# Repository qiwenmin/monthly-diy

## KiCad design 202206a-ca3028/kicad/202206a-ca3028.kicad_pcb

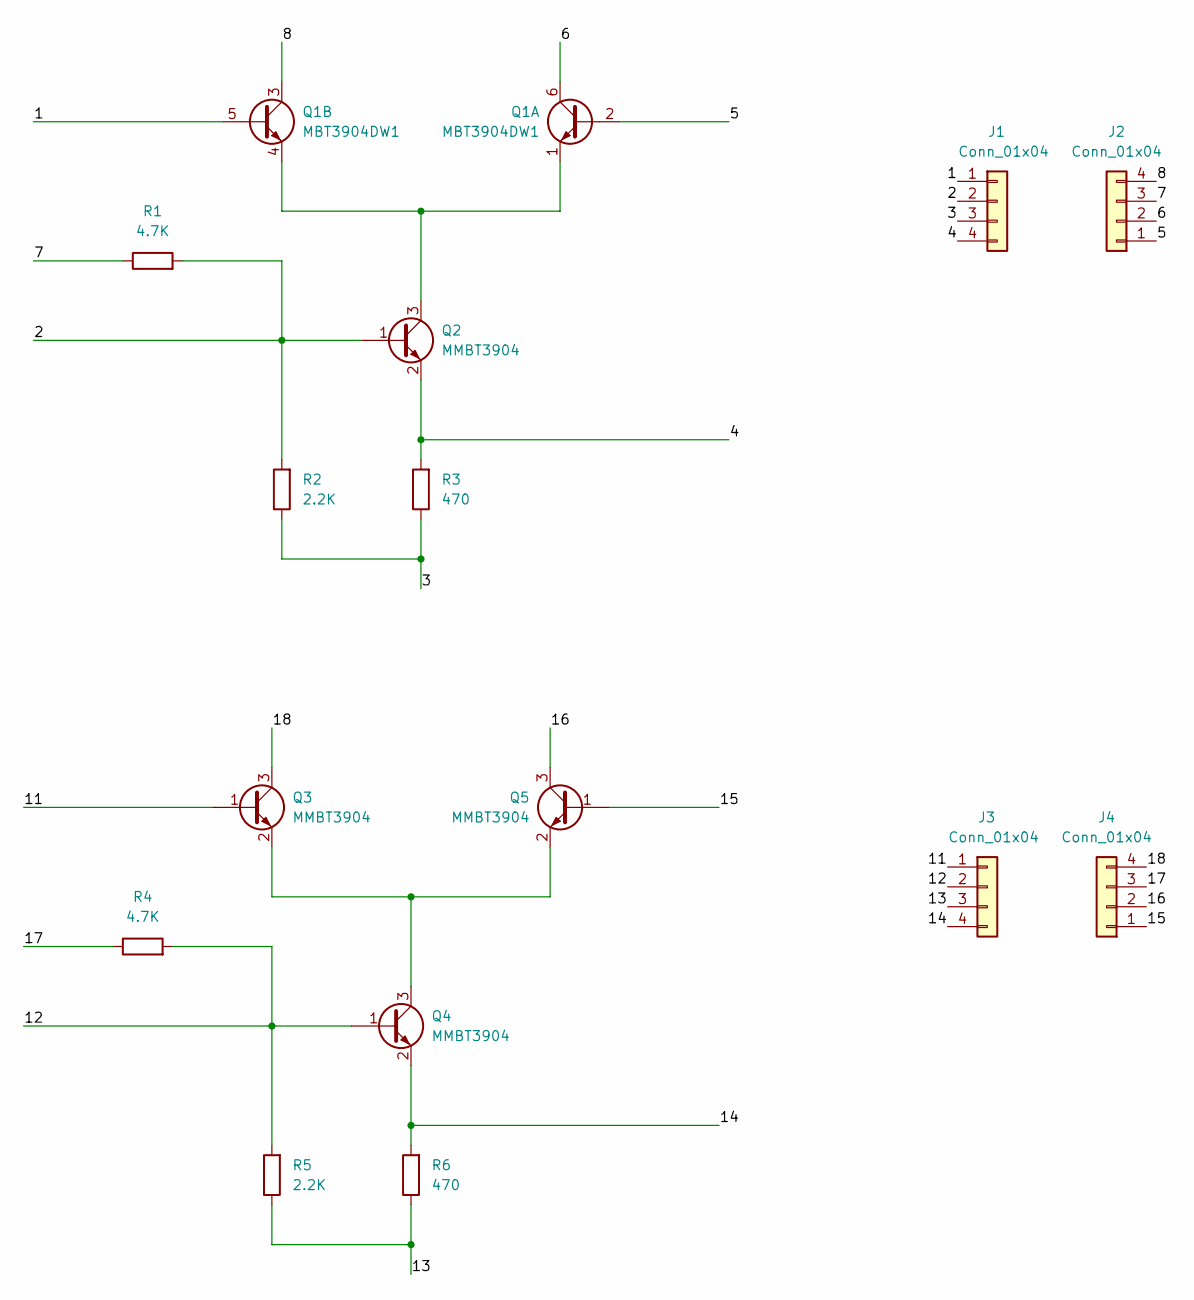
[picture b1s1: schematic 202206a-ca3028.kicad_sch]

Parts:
J1, J2, J3, J4: Conn_01x04; PinHeader_1x04_P2.54mm_Vertical
Q1: MBT3904DW1; SOT-363_SC-70-6
Q2, Q3, Q4, Q5: MMBT3904; SOT-23
R1, R4: 4.7K; R_0805_2012Metric
R2, R5: 2.2K; R_0805_2012Metric
R3, R6: 470; R_0805_2012Metric

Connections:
/1: J1.1, Q1.5 (B2)
/2: J1.2, Q2.1 (B), R1.2, R2.2
/3: J1.3, R2.1, R3.1
/4: J1.4, Q2.2 (E), R3.2
/5: J2.1, Q1.2 (B1)
/6: J2.2, Q1.6 (C1)
/7: J2.3, R1.1
/8: J2.4, Q1.3 (C2)
/11: J3.1, Q3.1 (B)
/12: J3.2, Q4.1 (B), R4.2, R5.2
/13: J3.3, R5.1, R6.1
/14: J3.4, Q4.2 (E), R6.2
/15: J4.1, Q5.1 (B)
/16: J4.2, Q5.3 (C)
/17: J4.3, R4.1
/18: J4.4, Q3.3 (C)
unnamed: Q1.1 (E1), Q1.4 (E2), Q2.3 (C)
unnamed: Q3.2 (E), Q4.3 (C), Q5.2 (E)

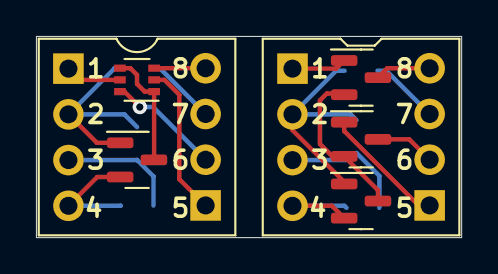
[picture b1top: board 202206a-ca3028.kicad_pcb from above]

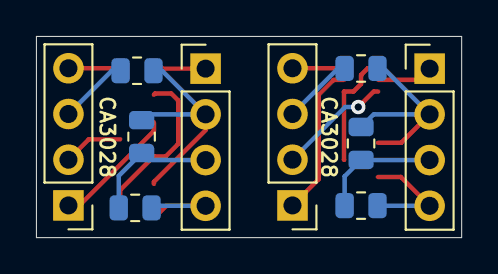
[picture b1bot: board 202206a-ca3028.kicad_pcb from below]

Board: 2 copper layers, 23.6 x 11.2 mm, 15 parts (10 on the bottom side), 18 nets.

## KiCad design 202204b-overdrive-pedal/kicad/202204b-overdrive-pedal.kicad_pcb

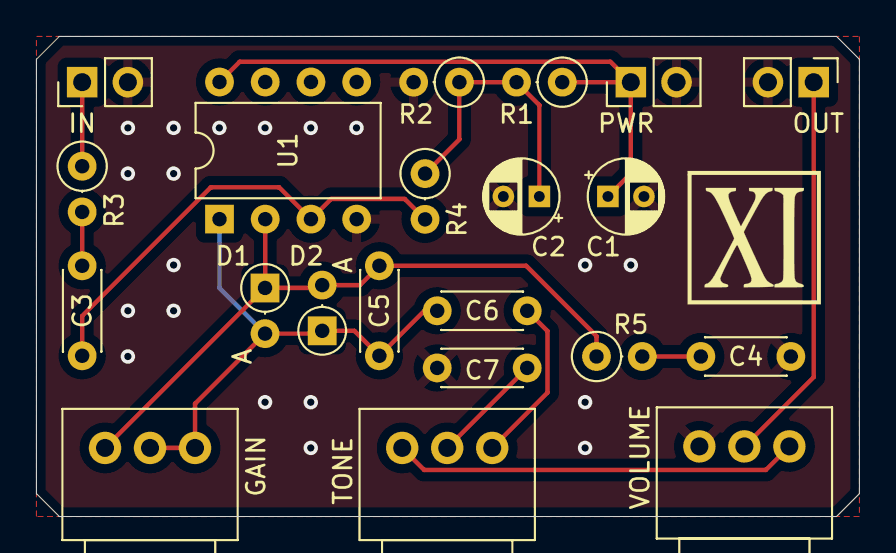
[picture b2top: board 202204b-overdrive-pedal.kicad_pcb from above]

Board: 2 copper layers, 45.7 x 26.7 mm, 21 parts (0 on the bottom side), 13 nets.

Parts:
C1, C2: 47u; CP_Radial_D4.0mm_P2.00mm
C3: 470n; C_Disc_D4.3mm_W1.9mm_P5.00mm
C4: 220n; C_Disc_D4.3mm_W1.9mm_P5.00mm
C5: 100p; C_Disc_D4.3mm_W1.9mm_P5.00mm
C6: 1u; C_Disc_D4.3mm_W1.9mm_P5.00mm
C7: 22n; C_Disc_D4.3mm_W1.9mm_P5.00mm
D1, D2: 1N4148; D_DO-35_SOD27_P2.54mm_Vertical_AnodeUp
J1: PWR; PinHeader_1x02_P2.54mm_Vertical
J2: IN; PinHeader_1x02_P2.54mm_Vertical
J3: OUT; PinHeader_1x02_P2.54mm_Vertical
R1, R2, R3: 10K; R_Axial_DIN0207_L6.3mm_D2.5mm_P2.54mm_Vertical
R4: 1M; R_Axial_DIN0207_L6.3mm_D2.5mm_P2.54mm_Vertical
R5: 1K; R_Axial_DIN0207_L6.3mm_D2.5mm_P2.54mm_Vertical
RV1: 500K; Potentiometer_Alps_RK097_Single_Horizontal
RV2: 10K; Potentiometer_Alps_RK097_Single_Horizontal
RV3: 100K; Potentiometer_Alps_RK097_Single_Horizontal
U1: LM358; DIP-8_W7.62mm

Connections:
/4.5V: C2.1, R1.2, R2.1, R4.1
/9V: C1.1, J1.1, R1.1, U1.8 (V+)
/IN: J2.1, R3.1
/OUT: J3.1, RV3.2
GND: C1.2, C2.2, C4.1, C7.1, J1.2, J2.2, J3.2, R2.2, RV3.1, U1.4 (V-)
unnamed: C3.1, R3.2
unnamed: C4.2, R5.2
unnamed: C6.2, RV2.3
unnamed: C7.2, RV2.2
unnamed: RV2.1, RV3.3
unnamed: C5.2, C6.1, D1.2 (A), D2.1 (K), RV1.2, RV1.3, U1.1
unnamed: C5.1, D1.1 (K), D2.2 (A), R5.1, RV1.1, U1.2 (-)
unnamed: C3.2, R4.2, U1.3 (+)

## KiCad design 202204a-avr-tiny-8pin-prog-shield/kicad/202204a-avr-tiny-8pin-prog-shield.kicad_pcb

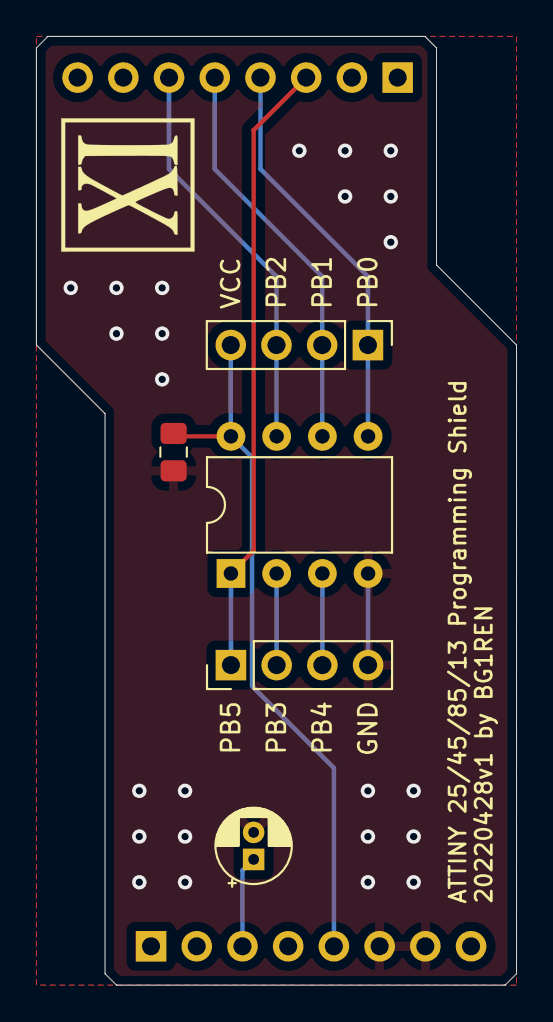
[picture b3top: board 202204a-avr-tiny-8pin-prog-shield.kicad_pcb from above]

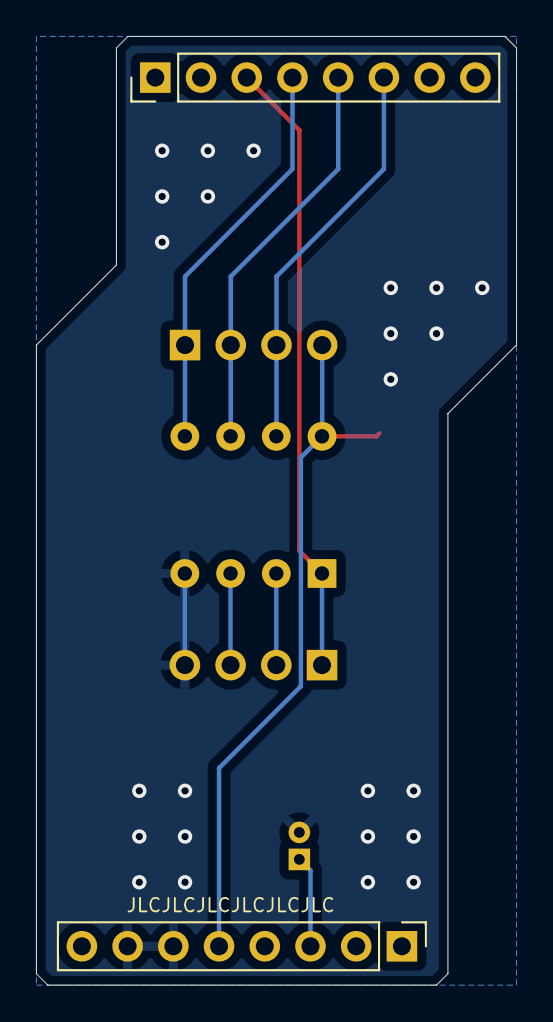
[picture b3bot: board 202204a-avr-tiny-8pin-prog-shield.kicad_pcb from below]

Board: 2 copper layers, 26.7 x 52.7 mm, 7 parts (2 on the bottom side), 9 nets.

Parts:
C1: 10u; CP_Radial_D4.0mm_P1.50mm
C2: 0.1u; C_0805_2012Metric_Pad1.18x1.45mm_HandSolder
J1: 1-4; PinHeader_1x04_P2.54mm_Vertical
J2: 5-8; PinHeader_1x04_P2.54mm_Vertical
J3: Arduino PWR; PinHeader_1x08_P2.54mm_Vertical
J4: Arduino Dx; PinHeader_1x08_P2.54mm_Vertical
U1: ATtiny85-20P; DIP-8_W7.62mm

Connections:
/PB0: J2.1, J4.4, U1.5 (AREF/PB0)
/PB1: J2.2, J4.5, U1.6 (PB1)
/PB2: J2.3, J4.6, U1.7 (PB2)
/PB3: J1.2, U1.2 (XTAL1/PB3)
/PB4: J1.3, U1.3 (XTAL2/PB4)
/PB5: J1.1, J4.3, U1.1 (~RESET/PB5)
/RESET: C1.1, J3.3
/VCC: C2.1, J2.4, J3.5, U1.8 (VCC)
GND: C1.2, C2.2, J1.4, J3.6, J3.7, U1.4 (GND)

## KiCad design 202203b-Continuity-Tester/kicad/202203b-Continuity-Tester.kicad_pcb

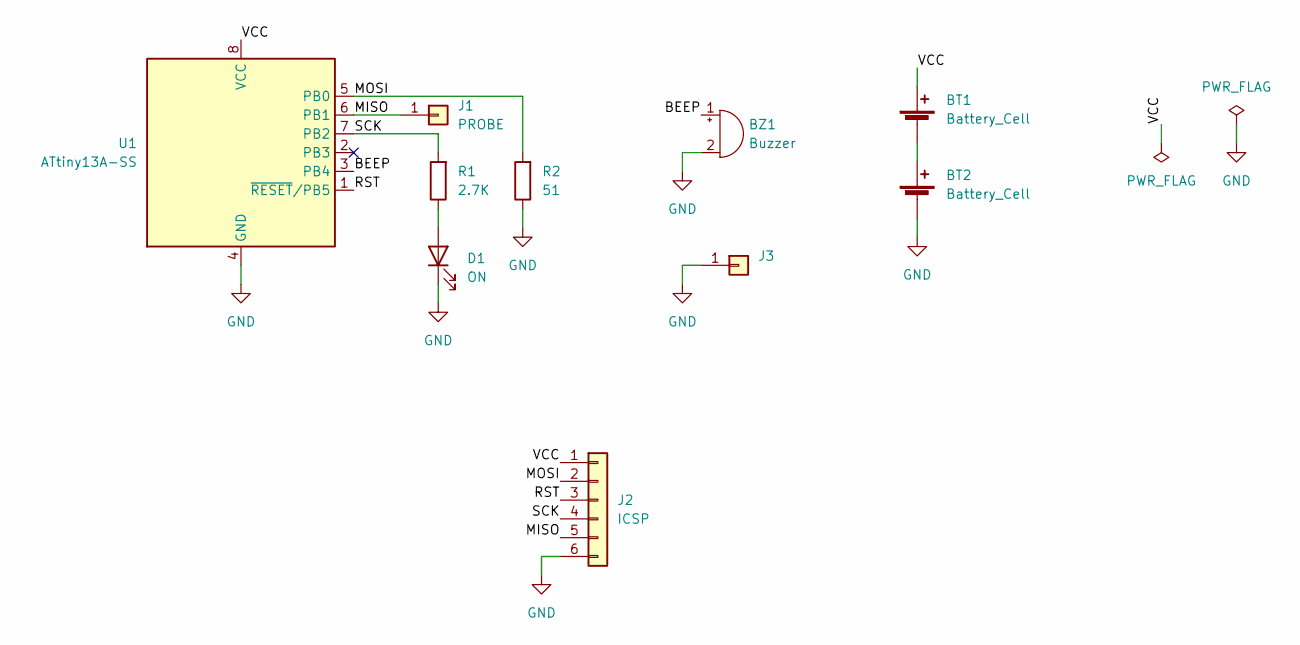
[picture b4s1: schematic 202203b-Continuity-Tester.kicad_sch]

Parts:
BT1, BT2: Battery_Cell; BatteryHolder_LR44_THT
BZ1: Buzzer; Buzzer_Murata_PKLCS1212E
D1: ON; LED_0805_2012Metric_Pad1.15x1.40mm_HandSolder
J1: PROBE; PinHeader_1x01_P2.54mm_Vertical
J2: ICSP; PinHeader_1x06_P2.00mm_Vertical
J3: (no value)
R1: 2.7K; R_0805_2012Metric_Pad1.20x1.40mm_HandSolder
R2: 51; R_0805_2012Metric_Pad1.20x1.40mm_HandSolder
U1: ATtiny13A-SS; SOIC-8_3.9x4.9mm_P1.27mm

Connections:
/BEEP: BZ1.1 (-), U1.3 (PB4)
/MISO: J1.1, J2.5, U1.6 (PB1)
/MOSI: J2.2, R2.2, U1.5 (PB0)
/RST: J2.3, U1.1 (~RESET/PB5)
/SCK: J2.4, R1.2, U1.7 (PB2)
/VCC: BT1.1 (+), J2.1, U1.8 (VCC)
GND: BT2.2 (-), BZ1.2 (+), D1.1 (K), J2.6, J3.1, R2.1, U1.4 (GND)
unnamed: BT1.2 (-), BT2.1 (+)
unnamed: D1.2 (A), R1.1

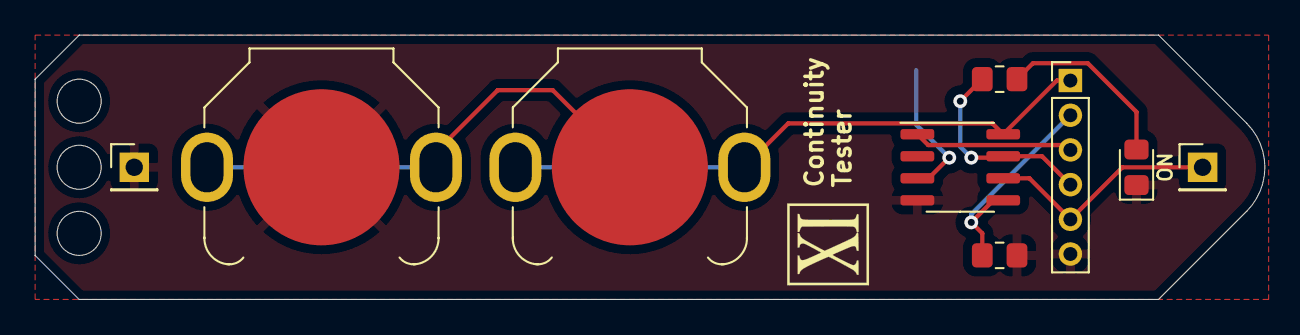
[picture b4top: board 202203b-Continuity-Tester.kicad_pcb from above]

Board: 2 copper layers, 70.9 x 15.2 mm, 10 parts (1 on the bottom side), 9 nets.

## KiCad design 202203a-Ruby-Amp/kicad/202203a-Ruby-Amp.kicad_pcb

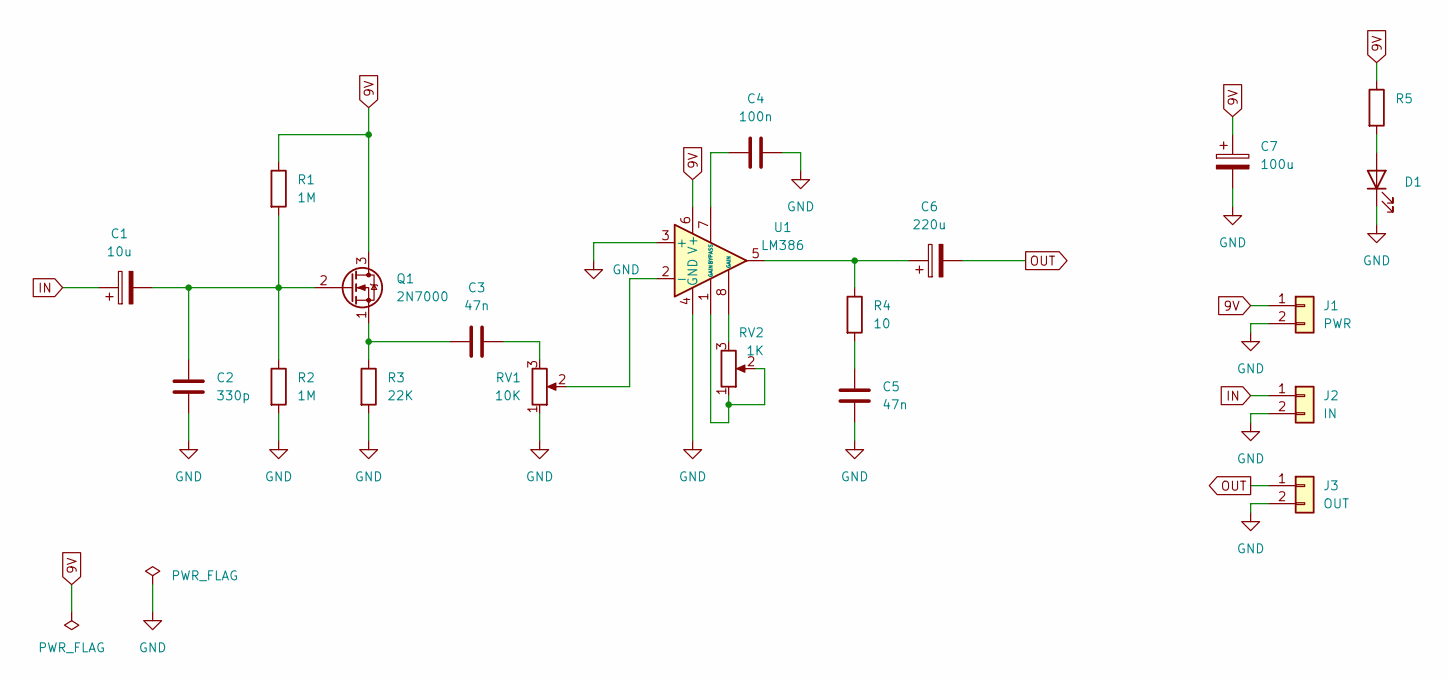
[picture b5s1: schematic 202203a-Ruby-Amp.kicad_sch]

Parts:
C1: 10u
C2: 330p; C_Disc_D4.3mm_W1.9mm_P5.00mm
C3, C5: 47n; C_Disc_D4.3mm_W1.9mm_P5.00mm
C4: 100n; C_Disc_D4.3mm_W1.9mm_P5.00mm
C6: 220u; CP_Radial_D6.3mm_P2.50mm
C7: 100u; CP_Radial_D5.0mm_P2.00mm
D1: (no value)
J1: PWR; JST_EH_B2B-EH-A_1x02_P2.50mm_Vertical
J2: IN; JST_EH_B2B-EH-A_1x02_P2.50mm_Vertical
J3: OUT; JST_EH_B2B-EH-A_1x02_P2.50mm_Vertical
Q1: 2N7000; TO-92_Inline_Wide
R1, R2: 1M; R_Axial_DIN0207_L6.3mm_D2.5mm_P2.54mm_Vertical
R3: 22K; R_Axial_DIN0207_L6.3mm_D2.5mm_P2.54mm_Vertical
R4: 10; R_Axial_DIN0207_L6.3mm_D2.5mm_P2.54mm_Vertical
R5: R_Axial_DIN0207_L6.3mm_D2.5mm_P2.54mm_Vertical
RV1: 10K; JST_EH_B3B-EH-A_1x03_P2.50mm_Vertical
RV2: 1K; JST_EH_B3B-EH-A_1x03_P2.50mm_Vertical
U1: LM386; DIP-8_W7.62mm

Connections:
9V: C7.1, J1.1, Q1.3 (D), R1.1, R5.1, U1.6 (V+)
GND: C2.2, C4.2, C5.2, C7.2, D1.1 (K), J1.2, J2.2, J3.2, R2.2, R3.2, RV1.1, U1.3 (+), U1.4 (GND)
IN: C1.1, J2.1
unnamed: C1.2, C2.1, Q1.2 (G), R1.2, R2.1
unnamed: C3.1, Q1.1 (S), R3.1
unnamed: C3.2, RV1.3
unnamed: C4.1, U1.7 (BYPASS)
unnamed: C5.1, R4.2
unnamed: C6.1, R4.1, U1.5
unnamed: D1.2 (A), R5.2
unnamed: RV1.2, U1.2 (-)
unnamed: RV2.1, RV2.2, U1.1 (GAIN)
unnamed: RV2.3, U1.8 (GAIN)
OUT: C6.2, J3.1

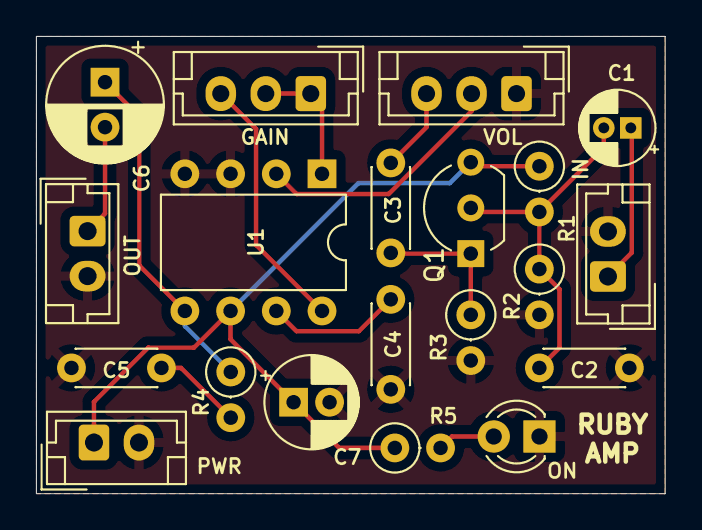
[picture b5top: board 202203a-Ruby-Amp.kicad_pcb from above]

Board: 2 copper layers, 34.9 x 25.4 mm, 20 parts (0 on the bottom side), 14 nets.

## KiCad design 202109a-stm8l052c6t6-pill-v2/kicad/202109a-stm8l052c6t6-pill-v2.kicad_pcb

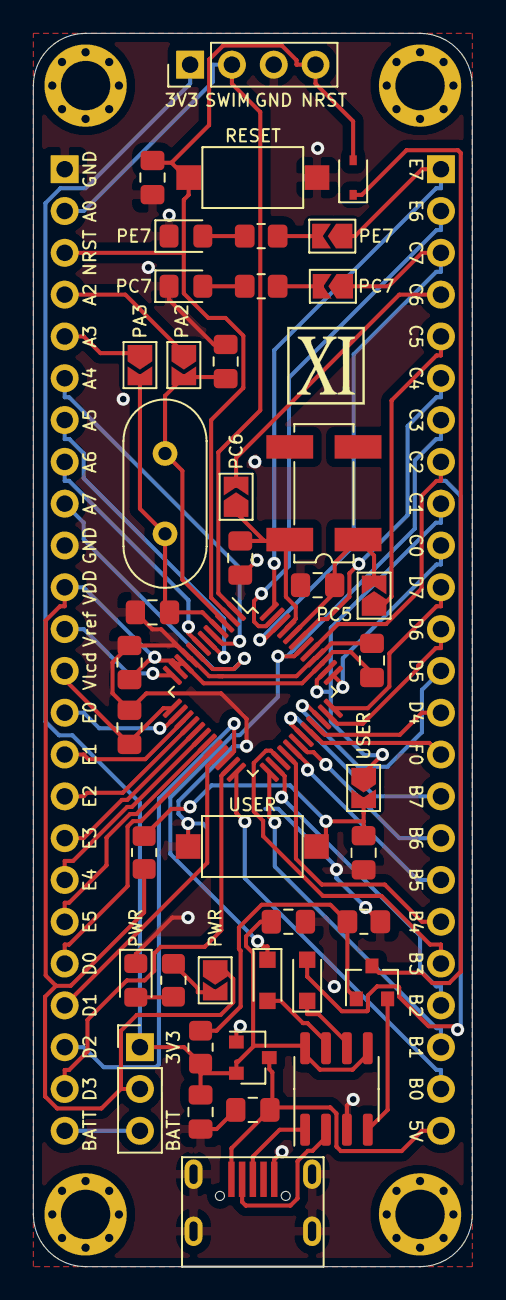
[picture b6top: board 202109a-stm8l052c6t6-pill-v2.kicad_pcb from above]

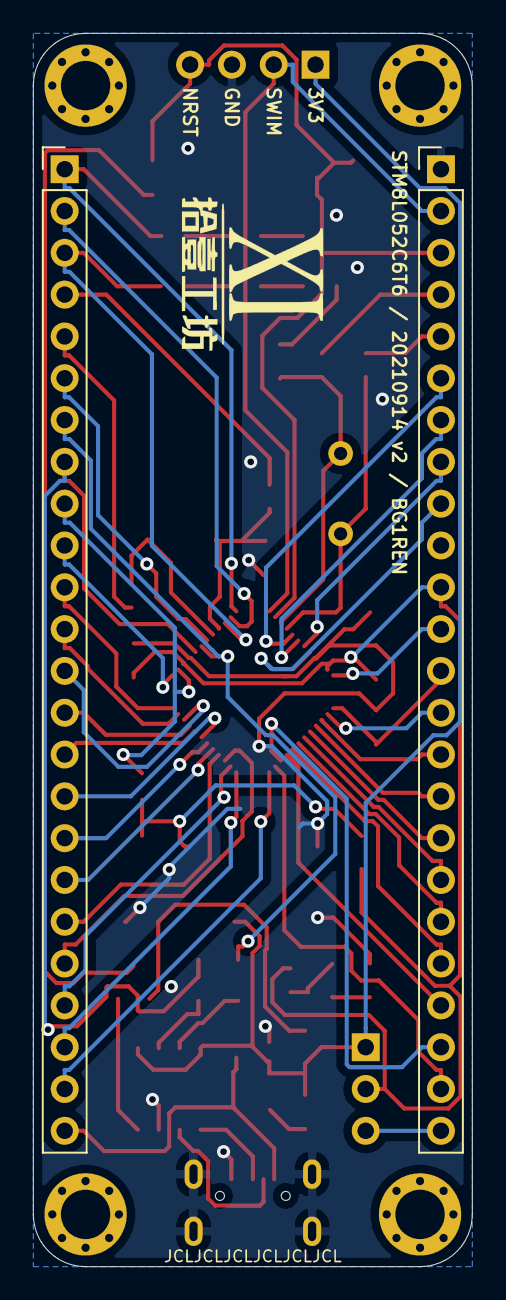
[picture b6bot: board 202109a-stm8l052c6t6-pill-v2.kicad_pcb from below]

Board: 2 copper layers, 26.7 x 74.9 mm, 51 parts (3 on the bottom side), 66 nets.

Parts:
C1, C2, C6, C9, C10, C11, C12: 100n; C_0805_2012Metric_Pad1.18x1.45mm_HandSolder
C3: 1u; C_0805_2012Metric_Pad1.18x1.45mm_HandSolder
C4, C5, C7, C8: 20p; C_0805_2012Metric_Pad1.18x1.45mm_HandSolder
D1, D2: 1N5819; D_SOD-323_HandSoldering
D3: PWR; LED_0805_2012Metric_Pad1.15x1.40mm_HandSolder
D4: PE7; LED_0805_2012Metric_Pad1.15x1.40mm_HandSolder
D5: PC7; LED_0805_2012Metric_Pad1.15x1.40mm_HandSolder
D6: 1N4148WS; D_SOD-323
G1: LOGO; xi-logo-c-05_05
G2: LOGO; xi-logo-a-10_09
H1, H2, H3, H4: MountingHole; MountingHole_3mm_Pad_Via
J1: PROG; PinHeader_1x04_P2.54mm_Vertical
J2: USB; MicroUSB5P-A01SB141B1-261
J3: PWR; PinHeader_1x03_P2.54mm_Vertical
J4: Header1; PinHeader_1x24_P2.54mm_Vertical
J5: Header2; PinHeader_1x24_P2.54mm_Vertical
JP1: PC5; SolderJumper-2_P1.3mm_Open_TrianglePad1.0x1.5mm
JP2: PC6; SolderJumper-2_P1.3mm_Open_TrianglePad1.0x1.5mm
JP3: PWR; SolderJumper-2_P1.3mm_Open_TrianglePad1.0x1.5mm
JP4: PA2; SolderJumper-2_P1.3mm_Open_TrianglePad1.0x1.5mm
JP5: PE7; SolderJumper-2_P1.3mm_Open_TrianglePad1.0x1.5mm
JP6: PA3; SolderJumper-2_P1.3mm_Open_TrianglePad1.0x1.5mm
JP7: PC7; SolderJumper-2_P1.3mm_Open_TrianglePad1.0x1.5mm
JP8: USER; SolderJumper-2_P1.3mm_Open_TrianglePad1.0x1.5mm
Q1: 2N7002; SOT-23
R1, R5: 1K; R_0805_2012Metric_Pad1.20x1.40mm_HandSolder
R2: 4.7K; R_0805_2012Metric_Pad1.20x1.40mm_HandSolder
R3: 680; R_0805_2012Metric_Pad1.20x1.40mm_HandSolder
R4: 10K; R_0805_2012Metric_Pad1.20x1.40mm_HandSolder
R6: 1M; R_0805_2012Metric_Pad1.20x1.40mm_HandSolder
SW1: RESET; SW_SPST_CK_RS282G05A3
SW2: USER; SW_SPST_CK_RS282G05A3
U1: STM8L052C6T6; LQFP-48_7x7mm_P0.5mm
U2: XC6206P332MR; SOT-23
U3: CH340N; SOIC-8_3.9x4.9mm_P1.27mm
Y1: 32.768K; Crystal_SMD_SeikoEpson_MC306-4Pin_8.0x3.2mm_HandSoldering
Y2: 16M; Crystal_HC49-4H_Vertical

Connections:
/3V3: C2.1, C6.1, J1.1, J3.1, R5.2, U2.2, U3.5, U3.8
/5V: C1.1, J2.1, J5.24, U2.3
/BATT: J3.3, J4.24
/HSE_IN: C7.1, JP4.2, U1.3, Y2.1
/HSE_OUT: C8.1, JP6.2, U1.4, Y2.2
/LSE_IN: C4.1, JP1.2, U1.44, Y1.1
/LSE_OUT: C5.1, JP2.1, U1.45, Y1.4
/NRST: C9.1, D6.2, J1.4, J4.3, SW1.2, U1.2
/PA0: J1.2, J4.2, U1.1
/PA2: J4.4, JP4.1
/PA3: J4.5, JP6.1
/PA4: J4.6, U1.5
/PA5: J4.7, U1.6
/PA6: J4.8, U1.7
/PA7: J4.9, U1.8
/PB0: J5.23, U1.24
/PB1: J5.22, U1.25
/PB2: J5.21, U1.26
/PB3: J5.20, U1.27
/PB4: J5.19, U1.28
/PB5: J5.18, U1.29
/PB6: J5.17, U1.30
/PB7: J5.16, U1.31
/PC0: J5.10, U1.37
/PC1: J5.9, JP8.1, U1.38
/PC2: D2.2, J5.8, U1.41
/PC3: D1.1, J5.7, U1.42
/PC4: J5.6, U1.43
/PC5: J5.5, JP1.1
/PC6: J5.4, JP2.2
/PC7: J5.3, JP7.1, U1.46
/PD0: J4.20, U1.20
/PD1: J4.21, U1.21
/PD2: J4.22, U1.22
/PD3: J4.23, U1.23
/PD4: J5.14, U1.33
/PD5: J5.13, U1.34
/PD6: J5.12, U1.35
/PD7: J5.11, U1.36
/PE0: J4.14, U1.14
/PE1: J4.15, U1.15
/PE2: J4.16, U1.16
/PE3: J4.17, U1.17
/PE4: J4.18, U1.18
/PE5: J4.19, U1.19
/PE6: J5.2, U1.47
/PE7: J5.1, JP5.1, U1.48
/PF0: J5.15, U1.32
/RTS: Q1.2, U3.4
/VDD: C11.1, C12.1, J3.2, J4.11, JP3.1, R4.1, U1.10, U1.11, U1.39
/VLCD: C3.1, J4.13, U1.13
/VREF: J4.12, U1.12
GND: C1.2, C2.2, C3.2, C4.2, C5.2, C6.2, C7.2, C8.2, C9.2, C10.2, C11.2, C12.2, D3.1, D4.1, D5.1, J1.3, J2.5, J2.6, J4.1, J4.10, R6.2, SW1.1, SW2.1, U1.9, U1.40, U2.1, U3.3
unnamed: C10.1, JP8.2, R4.2, SW2.2
unnamed: D1.2, U3.7
unnamed: D2.1, U3.6
unnamed: D3.2, R1.2
unnamed: D4.2, R2.2
unnamed: D5.2, R3.2
unnamed: D6.1, Q1.3
unnamed: J2.2, U3.2
unnamed: J2.3, U3.1
unnamed: JP3.2, R1.1
unnamed: JP5.2, R2.1
unnamed: JP7.2, R3.1
unnamed: Q1.1, R5.1, R6.1

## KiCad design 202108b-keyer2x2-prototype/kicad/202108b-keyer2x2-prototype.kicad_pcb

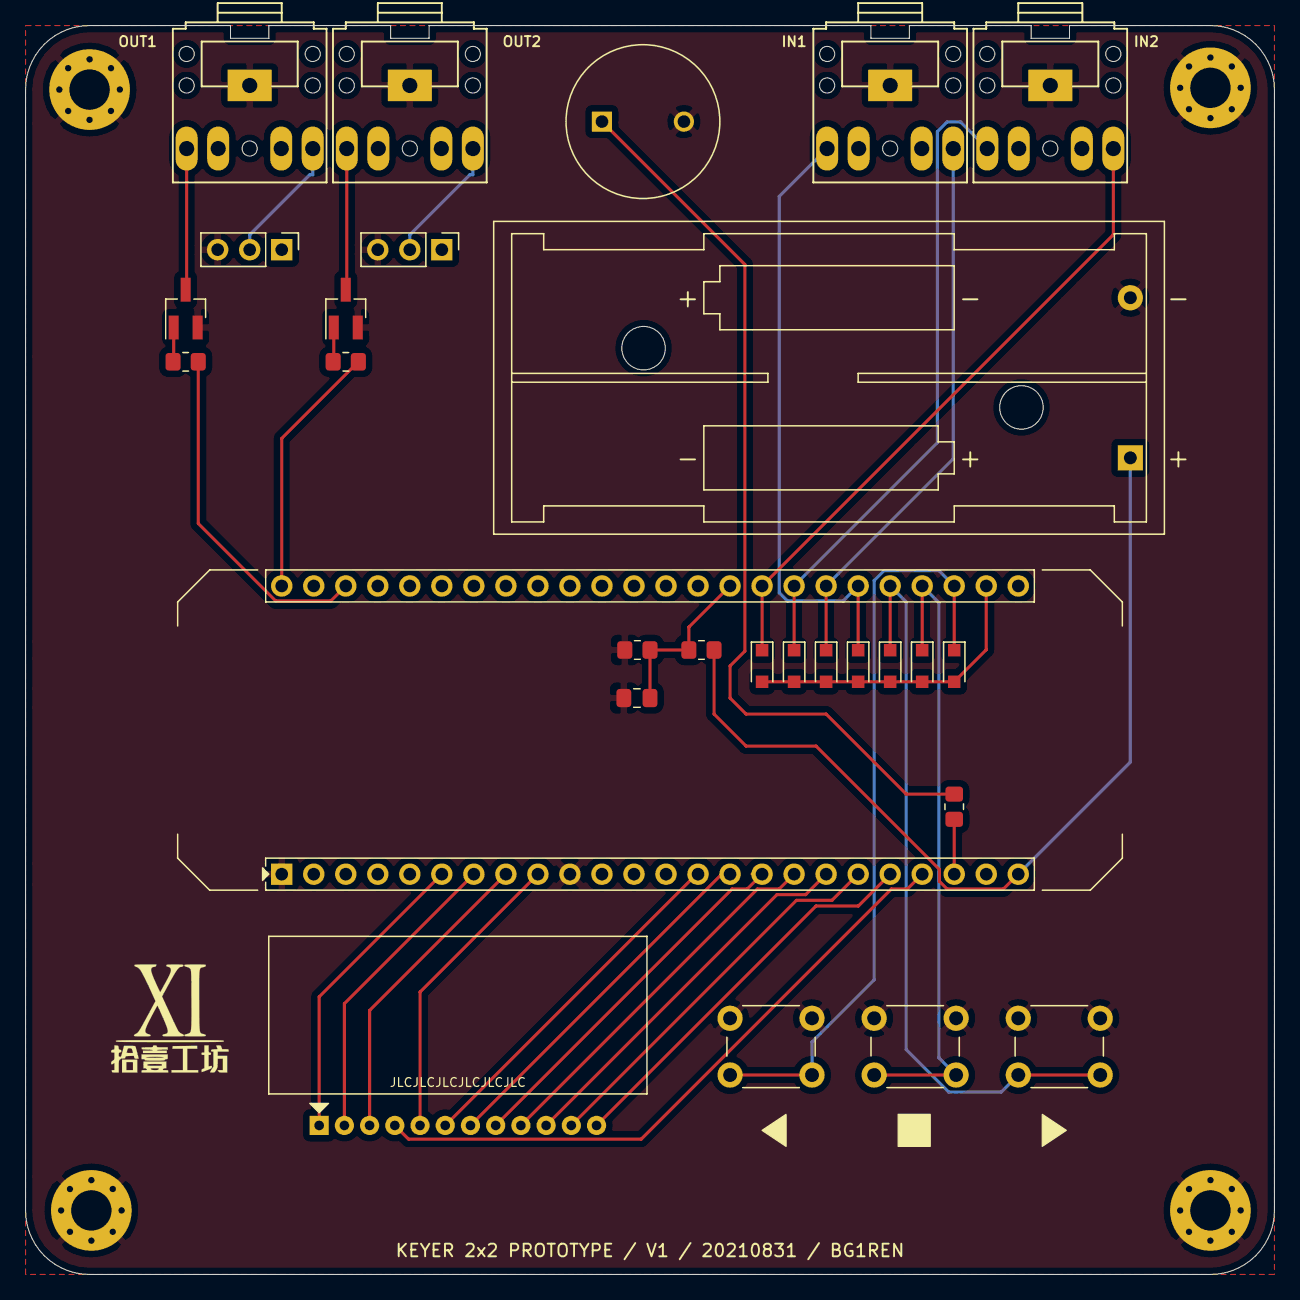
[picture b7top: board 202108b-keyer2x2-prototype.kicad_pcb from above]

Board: 2 copper layers, 99.1 x 99.1 mm, 32 parts (0 on the bottom side), 33 nets.

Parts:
BT1: 3V; BatteryHolder_Keystone_2468_2xAAA
C1: 100n; C_0805_2012Metric_Pad1.18x1.45mm_HandSolder
D1, D2, D3, D4, D5, D6, D7: 1N4148WS; D_SOD-323_HandSoldering
H1: M1; MountingHole_3.2mm_M3_Pad_Via
H2: M2; MountingHole_3.2mm_M3_Pad_Via
H3: M3; MountingHole_3.2mm_M3_Pad_Via
H4: M4; MountingHole_3.2mm_M3_Pad_Via
J1: R1GND; PinHeader_1x03_P2.54mm_Vertical
J2: OUT1; Tayda_3.5mm_stereo_TRS_jack_A-853
J3: R2GND; PinHeader_1x03_P2.54mm_Vertical
J4: OUT2; Tayda_3.5mm_stereo_TRS_jack_A-853
J5: IN1; Tayda_3.5mm_stereo_TRS_jack_A-853
J6: IN2; Tayda_3.5mm_stereo_TRS_jack_A-853
LS1: TONE; MagneticBuzzer_ProSignal_ABT-410-RC
Q1, Q2: 2N7002; SOT-23_Handsoldering
R1, R2: 10K; R_0805_2012Metric_Pad1.20x1.40mm_HandSolder
R3: 220; R_0805_2012Metric_Pad1.20x1.40mm_HandSolder
R4: 2M; R_0805_2012Metric_Pad1.20x1.40mm_HandSolder
R5: 1M; R_0805_2012Metric_Pad1.20x1.40mm_HandSolder
SW1: BTN_L; SW_PUSH_6mm_H4.3mm
SW2: BTN_M; SW_PUSH_6mm_H4.3mm
SW3: BTN_R; SW_PUSH_6mm_H4.3mm
U1: STM8L052C6T6-GreenPill-v1
U2: DISPLAY; LCD-SEG-4

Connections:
/ADC_IN: C1.1, R4.2, R5.1, U1.34
/BATT: BT1.1, R4.1, U1.24
/BTN_L: D1.1, SW1.2, U1.27
/BTN_M: D2.1, SW2.2, U1.28
/BTN_R: D3.1, SW3.2, U1.29
/COM0: U1.6, U2.1
/COM1: U1.7, U2.2
/COM2: U1.8, U2.3
/COM3: U1.21, U2.4
/DAH1: D5.1, J5.R, U1.31
/DAH2: D7.1, J6.R, U1.33
/DIT1: D4.1, J5.T, U1.30
/DIT2: D6.1, J6.T, U1.32
/KEYING1: R1.2, U1.46
/KEYING2: R2.2, U1.48
/SEG0: U1.9, U2.5
/SEG1: U1.14, U2.6
/SEG2: U1.15, U2.7
/SEG3: U1.16, U2.8
/SEG4: U1.17, U2.9
/SEG5: U1.18, U2.10
/SEG6: U1.19, U2.11
/SEG7: U1.20, U2.12
/SIDETONE: R3.2, U1.22
/WAKE: D1.2, D2.2, D3.2, D4.2, D5.2, D6.2, D7.2, U1.26
GND: BT1.2, C1.2, H1.1, H2.1, H3.1, H4.1, J1.3, J2.S, J3.3, J4.S, J5.S, J6.S, LS1.2, Q1.2, Q2.2, R5.2, SW1.1, SW2.1, SW3.1, U1.1, U1.10
unnamed: J1.2, J2.R
unnamed: J2.T, Q1.3
unnamed: J3.2, J4.R
unnamed: J4.T, Q2.3
unnamed: LS1.1, R3.1
unnamed: Q1.1, R1.1
unnamed: Q2.1, R2.1

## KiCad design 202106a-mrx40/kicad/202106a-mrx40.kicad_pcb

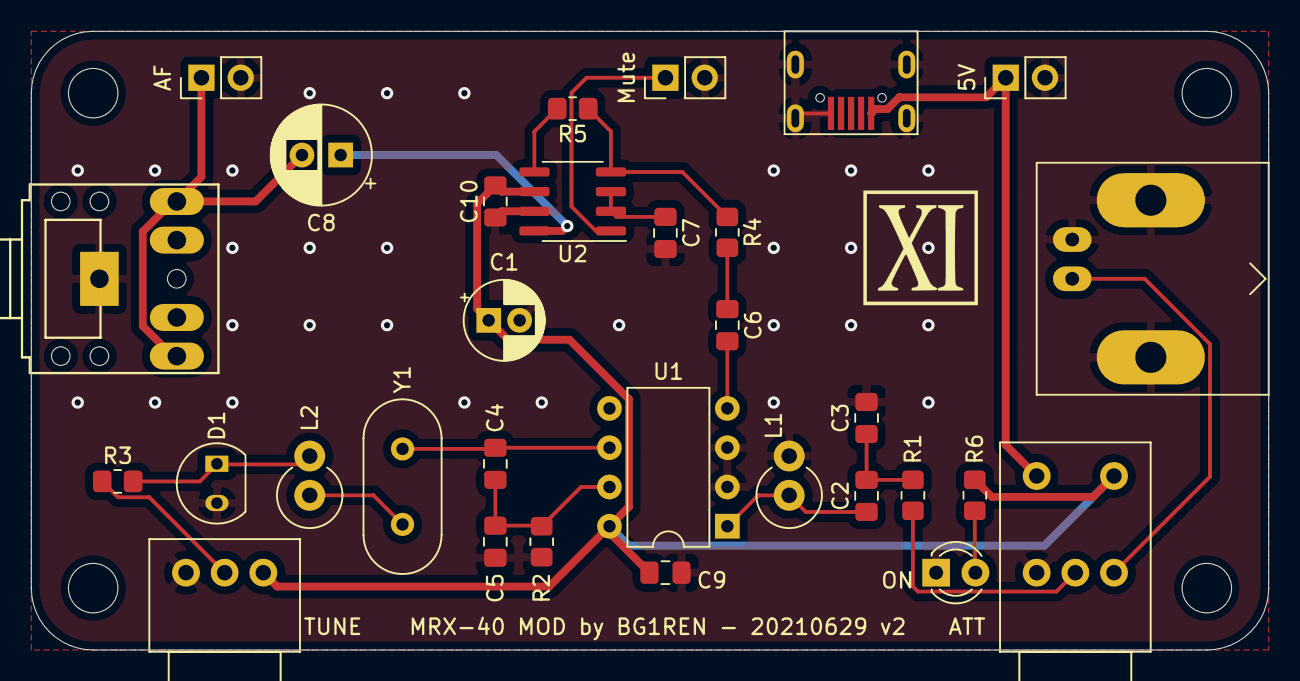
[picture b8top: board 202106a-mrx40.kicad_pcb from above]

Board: 2 copper layers, 80.0 x 40.0 mm, 31 parts (0 on the bottom side), 21 nets.

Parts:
AF1: AudioJack3_SwitchTR; Tayda_3.5mm_stereo_TRS_jack_A-853
C1: 220u; CP_Radial_D5.0mm_P2.00mm
C2: 91p; C_0805_2012Metric_Pad1.18x1.45mm_HandSolder
C3: 470p; C_0805_2012Metric_Pad1.18x1.45mm_HandSolder
C4: 270p; C_0805_2012Metric_Pad1.18x1.45mm_HandSolder
C5: 82p; C_0805_2012Metric_Pad1.18x1.45mm_HandSolder
C6, C7: 1u; C_0805_2012Metric_Pad1.18x1.45mm_HandSolder
C8: 470u; CP_Radial_D6.3mm_P2.50mm
C9, C10: 10n; C_0805_2012Metric_Pad1.18x1.45mm_HandSolder
D1: BB910; TO-92-2-21
D2: ON; LED_D3.0mm
J1: Ant; BNC_Amphenol_B6252HB-NPP3G-50_Horizontal
J2: Mute; PinHeader_1x02_P2.54mm_Vertical
J3: USB_B_Micro; MicroUSB5P-A01SB141B1-261
J4: 5V; PinHeader_1x02_P2.54mm_Vertical
J5: AF; PinHeader_1x02_P2.54mm_Vertical
L1: 5.6u; L_Axial_L9.5mm_D4.0mm_P2.54mm_Vertical_Fastron_SMCC
L2: 15u; L_Axial_L9.5mm_D4.0mm_P2.54mm_Vertical_Fastron_SMCC
R1: 47; R_0805_2012Metric_Pad1.20x1.40mm_HandSolder
R2, R6: 10K; R_0805_2012Metric_Pad1.20x1.40mm_HandSolder
R3: 100K; R_0805_2012Metric_Pad1.20x1.40mm_HandSolder
R4: 4.7K; R_0805_2012Metric_Pad1.20x1.40mm_HandSolder
R5: 470K; R_0805_2012Metric_Pad1.20x1.40mm_HandSolder
RV1: 10K; Potentiometer_Alps_RK097_Single_SW_Horizontal
RV2: 10K; Potentiometer_Alps_RK097_Single_Horizontal
U1: NE602; DIP-8_W7.62mm
U2: FM8002A; SOIC-8_3.9x4.9mm_P1.27mm
Y1: 7.023; Crystal_HC49-U_Vertical

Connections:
/5V: C1.1, C9.1, C10.2, R6.2, RV1.5, RV2.3, U1.8, U2.6
/5V_in: J3.1, J4.1, RV1.4
/AF: C6.2, U1.4
/AF_OUT: AF1.R, AF1.T, C8.2, J5.1
/ANT: J1.1, RV1.3
/MUTE: J2.1, U2.1
/RF: C2.2, C3.1, R1.1
GND: AF1.S, C1.2, C3.2, C5.2, C7.2, C9.2, C10.1, D1.2, D2.1, J1.2, J2.2, J3.5, J3.6, J4.2, J5.2, L1.2, R2.1, RV1.1, RV2.1, U1.2, U1.3, U2.7
unnamed: C2.1, L1.1, U1.1
unnamed: C4.1, C5.1, R2.2, U1.7
unnamed: C4.2, U1.6, Y1.1
unnamed: C6.1, R4.2
unnamed: C7.1, U2.2, U2.3
unnamed: C8.1, U2.8
unnamed: D1.1, L2.2, R3.2
unnamed: D2.2, R6.1
unnamed: L2.1, Y1.2
unnamed: R1.2, RV1.2
unnamed: R3.1, RV2.2
unnamed: R4.1, R5.1, U2.4
unnamed: R5.2, U2.5

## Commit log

2020-11-21 202011a
2020-11-22 Add README for 202011A
2020-11-28 Correct the probe resistor value to 2.2K
2020-11-29 Add 202011b
2020-11-30 Change PCB layout - 202011b-02
2020-12-22 2020-12 A
2020-12-22 Update ee-libs
2020-12-27 Add md202012b.
2021-01-24 New project can be created from a template
2021-01-24 Draw a MiniCore/UNO board.
2021-01-25 Add some labels on the B.SilkS layer.
    And update the settings of the pages.
2021-01-25 Update README.md for 202101A
2021-01-27 Add 202101b - UNO Proto Shield
2021-02-28 Add 202102a - Si5351 Beacon Shield
2021-02-28 Add 202102b - Si5351 Beacon LPF
2021-02-28 Update ee-libs to latest
2021-05-30 LM386 amp单点接地
2021-05-31 添加输出插座，并移动了LED
2021-05-31 增加了FM8002A的放大器
2021-05-31 增加了铺地的版本
2021-06-28 refactor: remove ee-libs from the project.
    Use `BG1REN_EE_LIBS_KICAD` path variable in KiCAD.
2021-06-28 202106a - MRX40
2021-06-28 Change the 3d models of the potentiometers.
2021-06-29 Fix BB910 pin error
2021-08-31 Add 202108a - STM8L052C6T6 GreenPill v1
2021-08-31 Add 202108b - Keyer 2x2 prototype v1
2021-09-14 Add 202109a - STM8L052C6T6 Pill v2
2022-03-30 Upgrade template from v5 to v6.
2022-03-30 Ruby Amp mod
2022-03-30 Generate new sheet uuid while creating project from the template
2022-03-31 Continuity Tester
2022-04-28 Add Arduino ATTiny 8-pin programming shield
2022-04-29 Add OverDrive Pedal
2022-06-28 Add CA3028
